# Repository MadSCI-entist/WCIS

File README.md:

WCIS – DIY Irrigation System Using ESP32

WCIS (Wirelessly Controlled Irrigation System) is an ESP32-based smart irrigation controller designed to control a solenoid valve for turning water flow ON and OFF automatically or manually.

WCIS uses an ESP32 microcontroller to control a DC solenoid valve through a MOSFET driver circuit.

The system can be expanded to include:

Scheduled irrigation (using NTP time)
Web-based control dashboard
Manual override

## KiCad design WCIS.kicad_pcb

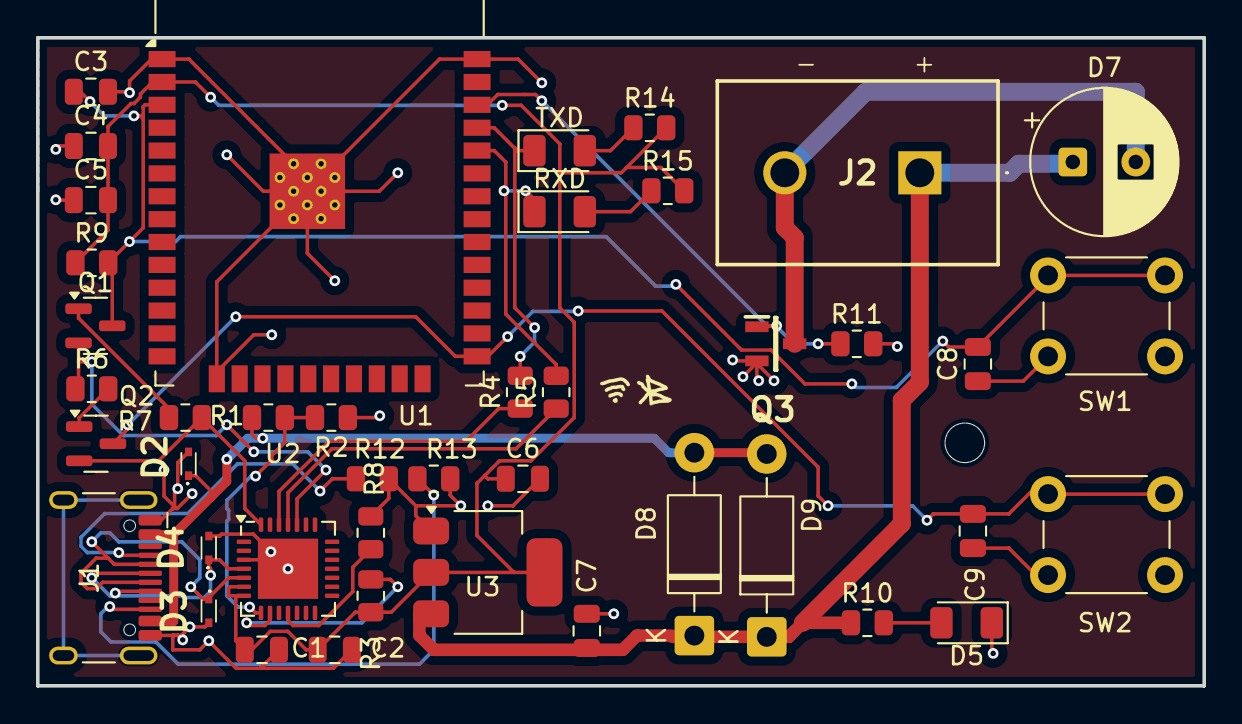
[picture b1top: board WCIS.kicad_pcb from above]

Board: 2 copper layers, 64.8 x 36.0 mm, 43 parts (0 on the bottom side), 26 nets.

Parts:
C1: 10uF/10V(20%); C_0805_2012Metric
C2, C3, C5: 0.1uF/50V(10%); C_0805_2012Metric
C4: 22uF/10V(20%); C_0805_2012Metric
C6, C7: 22uF; C_0805_2012Metric
C8, C9: 0.1uF; C_0805_2012Metric
D2, D3, D4: LESD5D5.0CT1G; LESD5D50CT1G
D5: LED; LED_1206_3216Metric
D7: 1000uF; CP_Radial_D8.0mm_P3.50mm
D8, D9: 1N5819; D_DO-41_SOD81_P10.16mm_Horizontal
J1: USB_C_Receptacle_USB2.0_14P; USB_C_Receptacle_HCTL_HC-TYPE-C-16P-01A
J2: Screw_Terminal_01x02; TB00475002GR
Q1, Q2: SS8050; SOT-23
Q3: IRLML2502TRPBF; SOT95P237X112-3N
R1: 22.1K(1%); R_0805_2012Metric
R2: 47.5k(1%); R_0805_2012Metric
R3: 2K(5%); R_0805_2012Metric
R4, R5: 0R; R_0805_2012Metric
R6, R7, R9: 10K(5%); R_0805_2012Metric
R8: 10K(5%)NC; R_0805_2012Metric
R10: 2K; R_0805_2012Metric
R11: 33K; R_0805_2012Metric
R12: 5.1k; R_0805_2012Metric
R13: 5.1K; R_0805_2012Metric
R14, R15: 2.2K; R_0805_2012Metric
RXD: LED; LED_1206_3216Metric
SW1, SW2: SW_Push; SW_PUSH_6mm_H4.3mm
TXD: LED; LED_1206_3216Metric
U1: ESP32-WROOM-32
U2: CP2102N-Axx-xQFN28; QFN-28-1EP_5x5mm_P0.5mm_EP3.35x3.35mm
U3: AMS1117-3.3; SOT-223-3_TabPin2

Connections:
/DTR: Q2.2 (E), R7.1, U2.28 (~DTR)
/EN: C3.1, C8.2, Q1.3 (C), R9.2, SW1.2, U1.3 (EN)
/IO0: C9.2, Q2.3 (C), SW2.2, U1.25 (IO0)
/RTS: Q1.2 (E), R6.1, U2.24 (~RTS)
/RXD: R5.1, U2.25 (RXD)
/RXD0: R5.2, RXD.1 (K), U1.34 (RXD0/IO3)
/TXD: R4.1, U2.26 (TXD)
/TXD0: R4.2, TXD.1 (K), U1.35 (TXD0/IO1)
/USB+: D4.1, J1.A6 (D+), J1.B6 (D+), U2.4 (D+)
/USB-: D3.1, J1.A7 (D-), J1.B7 (D-), U2.5 (D-)
GND: C1.1, C2.1, C3.2, C4.1, C5.1, C6.2, C7.2, C8.1, C9.1, D2.2, D3.2, D4.2, D5.1 (K), J1.A1 (GND), J1.A12 (GND), J1.B1 (GND), J1.B12 (GND), Q3.2 (S), R2.1, R8.2, R11.2, R12.2, R13.2, SW1.1, SW2.1, U1.1 (GND), U1.15 (GND), U1.38 (GND), U1.39 (GND), U2.3 (GND), U2.29 (GND), U3.1 (GND)
IN_5V: C7.1, D7.1, D8.1 (K), D9.1 (K), J2.1, R10.1, U3.3 (VI)
unnamed: R14.1, TXD.2 (A)
unnamed: D5.2 (A), R10.2
unnamed: R15.1, RXD.2 (A)
unnamed: J1.A5 (CC1), R12.1
unnamed: J1.B5 (CC2), R13.1
unnamed: D7.2, J2.2, Q3.3 (D)
unnamed: Q1.1 (B), R7.2
unnamed: Q2.1 (B), R6.2
unnamed: Q3.1 (G), R11.1, U1.36 (IO22)
unnamed: R1.2, R2.2, U2.8 (VBUS)
unnamed: R3.2, U2.9 (~RST)
unnamed: R8.1, U2.11 (~SUSPEND)
VBUS: D2.1, D8.2 (A), D9.2 (A), J1.A4 (VBUS), J1.A9 (VBUS), J1.B4 (VBUS), J1.B9 (VBUS), R1.1
VDD33: C1.2, C2.2, C4.2, C5.2, C6.1, R3.1, R9.1, R14.2, R15.2, U1.2 (VDD), U2.6 (VDD), U2.7 (VREGIN), U3.2 (VO)

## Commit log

2025-12-27 KICAD files
2025-12-27 Add README for WCIS irrigation system
    Added project overview and features for WCIS.
2025-12-27 Bill Of Materials
2025-12-27 Update WCIS.csv to add missing entries
